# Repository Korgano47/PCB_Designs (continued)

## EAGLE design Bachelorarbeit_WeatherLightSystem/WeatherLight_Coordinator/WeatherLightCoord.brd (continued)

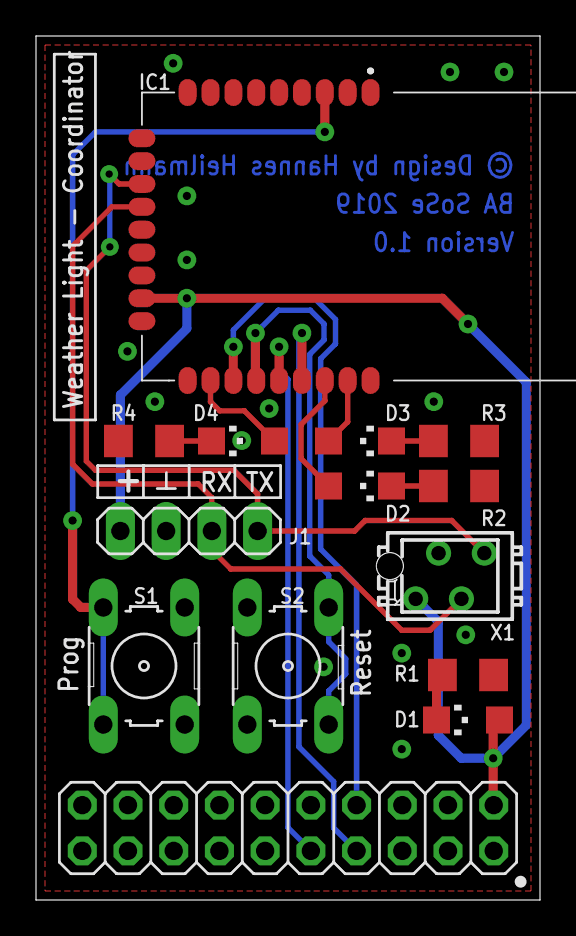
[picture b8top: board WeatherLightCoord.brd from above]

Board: 2 copper layers, 28.0 x 48.0 mm, 14 parts (0 on the bottom side), 16 nets.

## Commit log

2023-04-18 First test
2023-04-18 test 2
2023-04-19 HP25E added
2023-04-19 Added EAGLE examples
2023-04-19 Added zips
